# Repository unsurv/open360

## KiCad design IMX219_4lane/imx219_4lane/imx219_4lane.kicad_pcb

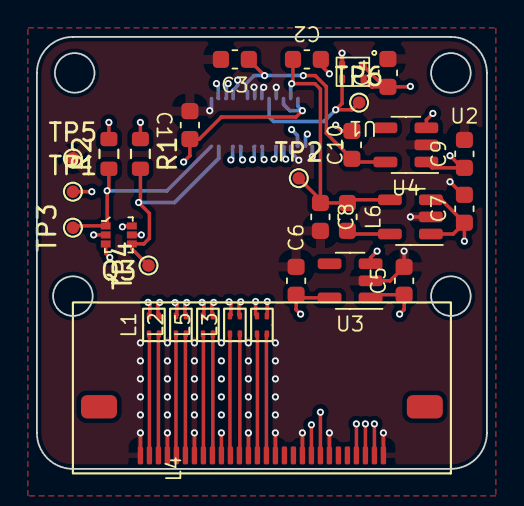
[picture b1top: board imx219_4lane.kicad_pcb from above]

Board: 4 copper layers, 25.0 x 24.0 mm, 31 parts (1 on the bottom side), 32 nets.

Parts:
C1, C2, C3, C5, C6, C9, C10: 1uF; C_0603_1608Metric
C4: 0.1uF; C_0603_1608Metric
C7: 4.7uF; C_0603_1608Metric
C8: 10uF; C_0603_1608Metric
J1: DF37NC-30DS-0.4V; DF37NC-30DS
J2: FPC 28 pin connector; Molex 505110-2891
L1, L2, L3, L4, L5: DLP11SN900HL2L; DLP11SN900HL2L_hand_solder
L6: 10uF; C_0603_1608Metric
Q3: NTZD3154N; SOT-563
R1, R2: 2K2; R_0603_1608Metric
TP1, TP2, TP3, TP4, TP5, TP6: TestPoint; TestPoint_Pad_D0.7mm
U1: AMPM; AMPM oscillator
U2: LM3670MF; SOT-23-5
U3, U4: AP7331; SOT-23-5

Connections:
+1V2: C2.1, C8.1, J1.4 (VD1V2), L6.1, TP2.1, U2.4 (FB)
+1V8: C1.1, C4.1, C6.1, J1.3 (VO1V8), J1.5 (/PWDN), Q3.2 (G2), Q3.5 (G1), R1.1, R2.1, TP1.1, U1.1 (OE), U1.4 (VDD), U3.5 (OUT)
+2V8: C3.1, C10.1, J1.10 (VA2V8), U4.5 (OUT)
+5V: C5.1, C7.1, C9.1, J2.2, J2.3, J2.4, U2.1 (Vin), U2.3 (EN), U3.1 (IN), U3.3 (EN), U4.1 (IN), U4.3 (EN)
CSI_CLKN: J1.26 (MCKN), L5.3
CSI_CLKP: J1.27 (MCKP), L5.2
CSI_D0N: J1.23 (MD0N), L4.3
CSI_D0P: J1.24 (MD0P), L4.2
CSI_D1N: J1.20 (MD1N), L3.3
CSI_D1P: J1.21 (MD1P), L3.2
CSI_D2N: J1.17 (MD2N), L2.3
CSI_D2P: J1.18 (MD2P), L2.2
CSI_D3N: J1.14 (MD3N), L1.3
CSI_D3P: J1.13 (MD3P), L1.2
GND: C1.2, C2.2, C3.2, C4.2, C5.2, C6.2, C7.2, C8.2, C9.2, C10.2, J1.6 (DGND4), J1.8 (DGND3), J1.9 (AGND), J1.12 (DGND2), J1.15 (DGND1), J1.16 (DGND5), J1.19 (DGND6), J1.22 (DGND7), J1.25 (DGND8), J1.28 (DGND9), J2.1, J2.7, J2.10, J2.13, J2.16, J2.19, J2.22, J2.25, J2.28, TP5.1, U1.2 (GND), U2.2 (GND), U3.2 (GND), U4.2 (GND)
I2C_SCL_3V3: J2.9, Q3.3 (D1)
I2C_SDA_3V3: J2.8, Q3.6 (D2)
MCLK: J1.7 (MCLK), TP6.1, U1.3 (OUT)
MIPI_CLK_N: J2.20, L5.4
MIPI_CLK_P: J2.21, L5.1
MIPI_DATA_0_N: J2.14, L4.4
MIPI_DATA_0_P: J2.15, L4.1
MIPI_DATA_1_N: J2.17, L3.4
MIPI_DATA_1_P: J2.18, L3.1
MIPI_DATA_2_N: J2.23, L2.4
MIPI_DATA_2_P: J2.24, L2.1
MIPI_DATA_3_N: J2.26, L1.4
MIPI_DATA_3_P: J2.27, L1.1
unnamed: L6.2, U2.5 (SW)
SCL_1V8: J1.29 (SCL), Q3.4 (S1), R1.2, TP4.1
SDA_1V8: J1.30 (SDA), Q3.1 (S2), R2.2, TP3.1
SHELL: J2.29, J2.30

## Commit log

2023-01-22 added schematic for 4 lane IMX219
    adapted from raspi schematic and diy 4 lane schematic
2023-02-05 new footprint, PCB parts placement
2023-02-08 zone concept
2023-02-11 added dual channel mosfet for 1v8 I2C
2023-02-11 length matching mipi signals
2023-02-12 prototype routing
2023-02-14 flip connector -.-
2023-02-15 fix 1V2 layout
